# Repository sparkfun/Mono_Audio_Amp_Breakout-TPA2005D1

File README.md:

SparkFun Mono Audio Amp Breakout - TPA2005D1
========================================

[*SparkFun Mono Audio Amp Breakout - TPA2005D1 (BOB-11044)*](https://www.sparkfun.com/products/11044)

This tiny audio amplifier is based on the Texas Instruments TPA2005D1. 
Its efficient class-D operation means low heat and long battery life. 
It can drive an 8-Ohm speaker at up to 1.4 Watts; it won’t shake a stadium, but it will provide plenty of volume for your audio projects.

Repository Contents
-------------------

* **/Hardware** - Eagle design files (.brd, .sch)
* **/Production** - Production panel files (.brd)

Documentation
--------------
* **[Hookup Guide](https://www.sparkfun.com/tutorials/392)** - Basic hookup guide for the Mono Audio Amplifier.
* **[SparkFun Fritzing repo](https://github.com/sparkfun/Fritzing_Parts)** - Fritzing diagrams for SparkFun products.
* **[SparkFun 3D Model repo](https://github.com/sparkfun/3D_Models)** - 3D models of SparkFun products. 

License Information
-------------------
This product is _**open source**_! 

The **hardware** is released under [Creative Commons ShareAlike 4.0 International](https://creativecommons.org/licenses/by-sa/4.0/).

Please use, reuse, and modify these files as you see fit. Please maintain attribution to SparkFun Electronics and release anything derivative under the same license.

Distributed as-is; no warranty is given.

- Your friends at SparkFun.

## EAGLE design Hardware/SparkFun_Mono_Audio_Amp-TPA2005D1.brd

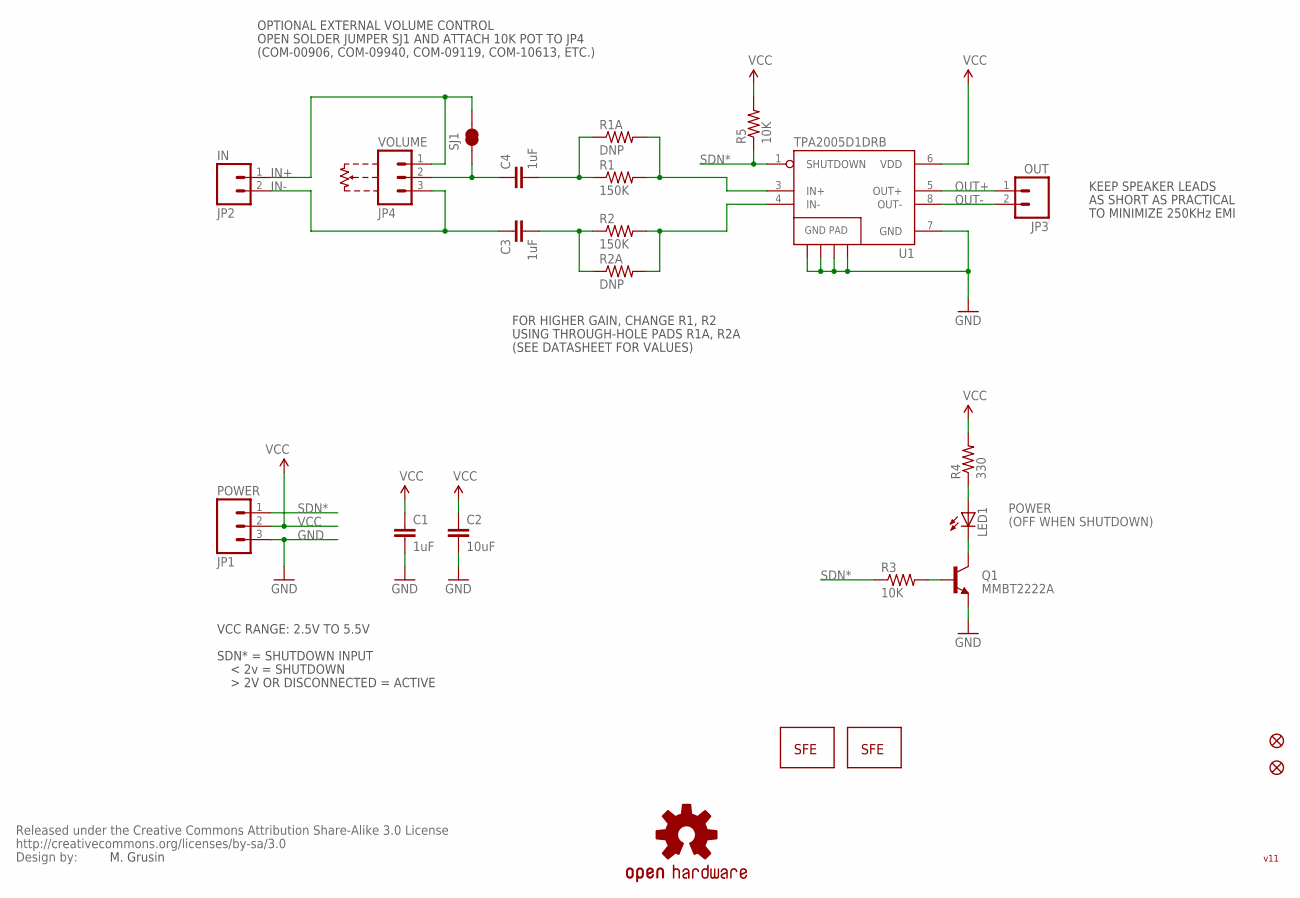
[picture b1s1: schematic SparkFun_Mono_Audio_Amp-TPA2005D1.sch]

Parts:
C1, C3, C4: 1uF; 1206
C2: 10uF; 1206
JP1: POWER; 1X03
JP2: IN; 1X02
JP3: OUT; 1X02
JP4: VOLUME; 1X03
JP5, JP6: FIDUCIALUFIDUCIAL; MICRO-FIDUCIAL
LED1: LED0603; LED-0603
LOGO1: LOGO-SFENW2; SFE-NEW-WEB
LOGO2: LOGO-SFESK; SFE-LOGO-FLAME
Q1: MMBT2222A; SOT23-3
R1, R2: 150K; 0603-RES
R1A, R2A: DNP; AXIAL-0.3
R3, R5: 10K; 0603-RES
R4: 330; 0603-RES
SJ1: SOLDERJUMPERNC2; SJ_2S-NOTRACE
U1: TPA2005D1DRB; QFN-8_PAD
U$1: CREATIVE_COMMONS
U$2: OSHW-LOGOS; OSHW-LOGO-S

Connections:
GND: C1.2, C2.2, JP1.3, Q1.2 (E), U1.7 (GND), U1.10 (GND), U1.11 (GND), U1.12 (GND), U1.13 (GND)
IN+: JP2.1, JP4.1, SJ1.2
IN+AMP: R1.2, R1A.P$2 (2), U1.3 (IN+)
IN-: C3.1, JP2.2, JP4.3
IN-AMP: R2.2, R2A.P$2 (2), U1.4 (IN-)
unnamed: C4.1, JP4.2, SJ1.1
unnamed: C4.2, R1.1, R1A.P$1 (1)
unnamed: C3.2, R2.1, R2A.P$1 (1)
unnamed: LED1.C, Q1.3 (C)
unnamed: LED1.A, R4.1
unnamed: Q1.1 (B), R3.2
OUT+: JP3.1, U1.5 (OUT+)
OUT-: JP3.2, U1.8 (OUT-)
SDN*: JP1.1, R3.1, R5.1, U1.1 (SHUTDOWN)
VCC: C1.1, C2.1, JP1.2, R4.2, R5.2, U1.6 (VDD)

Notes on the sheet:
POWER
(OFF WHEN SHUTDOWN)
OPEN SOLDER JUMPER SJ1 AND ATTACH 10K POT TO JP4
OPTIONAL EXTERNAL VOLUME CONTROL
M. Grusin
FOR HIGHER GAIN, CHANGE R1, R2
USING THROUGH-HOLE PADS R1A, R2A
(SEE DATASHEET FOR VALUES)
SDN* = SHUTDOWN INPUT
< 2v = SHUTDOWN
VCC RANGE: 2.5V TO 5.5V
(COM-00906, COM-09940, COM-09119, COM-10613, ETC.)
KEEP SPEAKER LEADS
AS SHORT AS PRACTICAL
TO MINIMIZE 250KHz EMI
v11

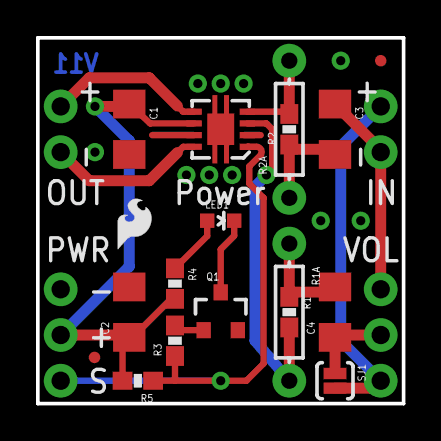
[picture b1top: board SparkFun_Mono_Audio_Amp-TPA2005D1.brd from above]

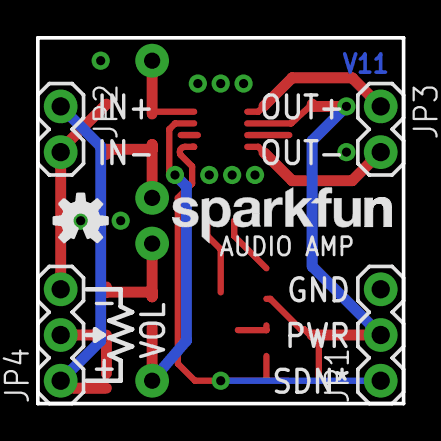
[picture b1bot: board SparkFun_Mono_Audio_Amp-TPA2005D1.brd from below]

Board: 2 copper layers, 20.3 x 20.3 mm, 25 parts (6 on the bottom side), 15 nets.

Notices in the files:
parts and their libraries:
SparkFun: Released under the Creative Commons Attribution Share-Alike 3.0 License
SparkFun: http://creativecommons.org/licenses/by-sa/3.0
SparkFun-Aesthetics: Licensing: CC v3.0 Share-Alike You are welcome to use this library for commercial purposes.
